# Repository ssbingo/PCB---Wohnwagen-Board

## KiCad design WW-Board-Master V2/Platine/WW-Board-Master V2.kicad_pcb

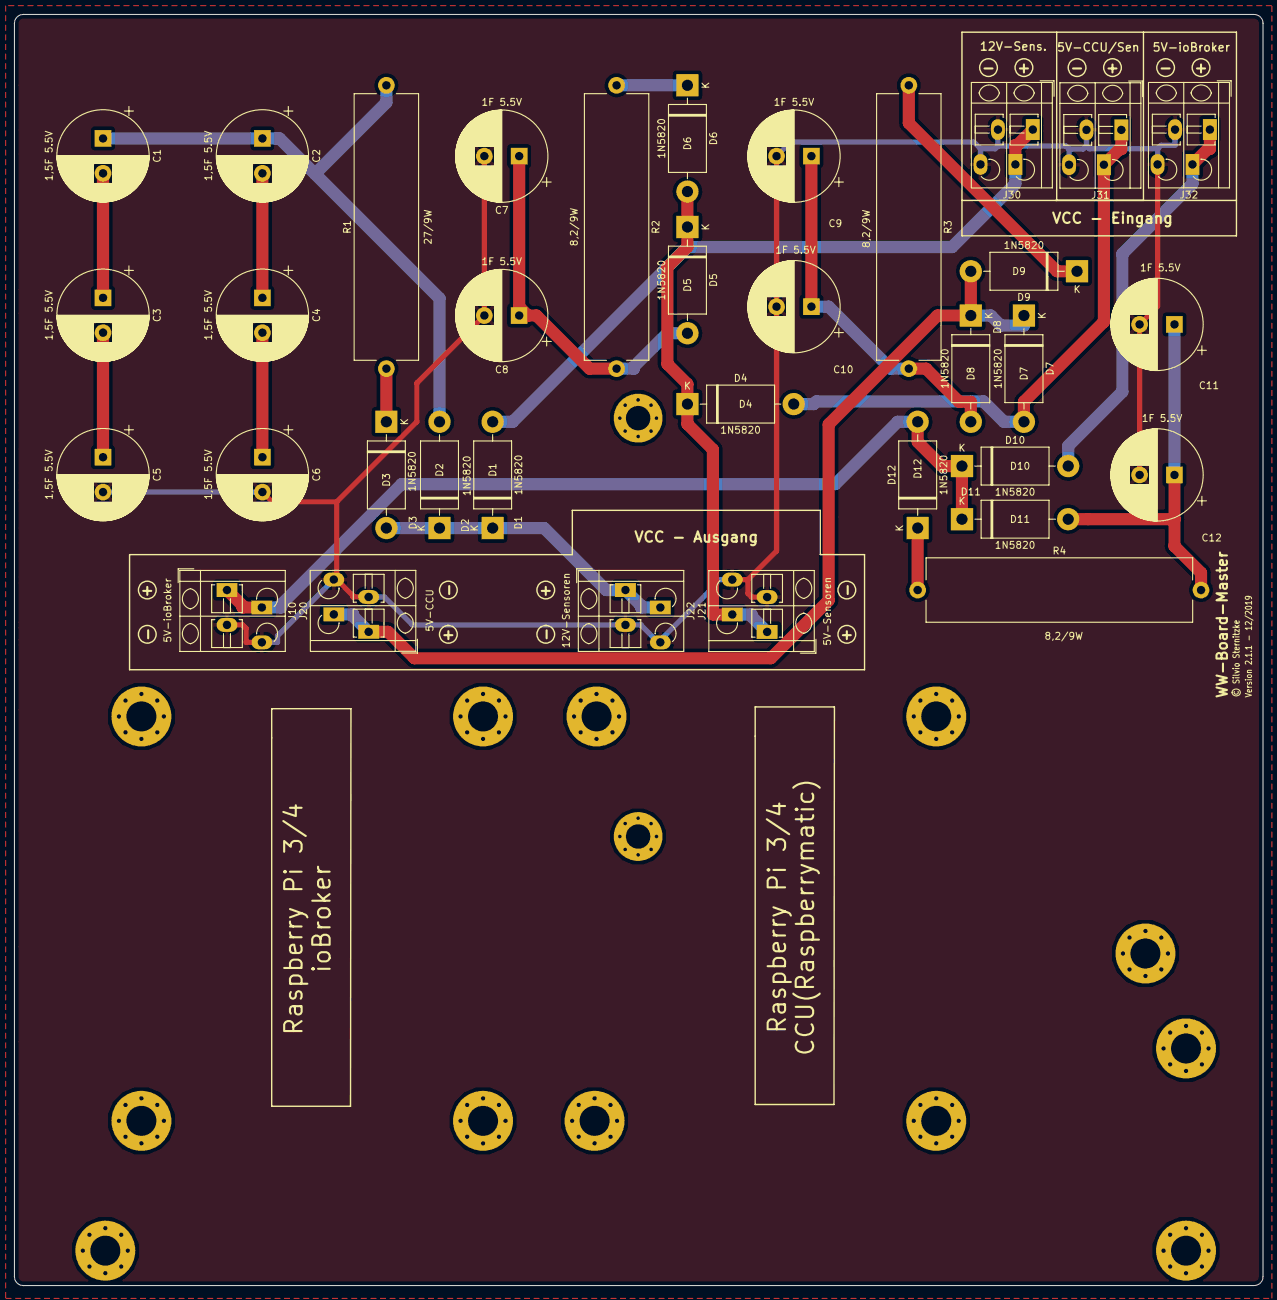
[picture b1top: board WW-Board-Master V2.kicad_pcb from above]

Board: 2 copper layers, 179.1 x 182.3 mm, 51 parts (1 on the bottom side), 20 nets.

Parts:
C1, C2, C3, C4, C5, C6: 1,5F 5.5V; CP_Radial_D21.0mm_P5.00mm
C7, C8, C9, C10, C11, C12: 1F 5.5V; CP_Radial_D20.0mm_P5.00mm
D1, D2, D3, D4, D5, D6, D7, D8, D9, D10, D11, D12: 1N5820; D_DO-201AD_P15.24mm_Horizontal
J10, J32: 5V-ioBroker; TerminalBlock_WAGO_804-102_1x02_P5.00mm_45Degree
J20: 5V-CCU; TerminalBlock_WAGO_804-102_1x02_P5.00mm_45Degree
J21: 5V-Sensoren; TerminalBlock_WAGO_804-102_1x02_P5.00mm_45Degree
J22: 12V-Sensoren; TerminalBlock_WAGO_804-102_1x02_P5.00mm_45Degree
J30: 12V-Sens.; TerminalBlock_WAGO_804-102_1x02_P5.00mm_45Degree
J31: 5V-CCU/Sen; TerminalBlock_WAGO_804-102_1x02_P5.00mm_45Degree
Logo1, Logo2: Version 2.1.1 - 12/2019; Copyrigth
R1: 27/9W; R_Axial_Power_L38.0mm_W9.0mm_P40.64mm
R2, R3, R4: 8,2/9W; R_Axial_Power_L38.0mm_W9.0mm_P40.64mm
REF05: MountingHole_4.3mm_M4_Pad_Via
REF_01, REF_02, REF_03, REF_04, REF_06, REF_07, REF_08, REF_09_1, REF_09_2, REF_09_3, REF_09_4: MountingHole_4.3mm_M4_Pad_Via
REF_S1, REF_S2: MountingHole_3.5mm_Pad_Via

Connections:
GND: C5.2, C6.2, C7.2, C8.2, C9.2, C10.2, C11.2, C12.2, J10.2, J20.2, J21.2, J22.2, J30.2, J31.2, J32.2
unnamed: C1.1, C2.1, D2.2, R1.2
unnamed: C1.2, C3.1
unnamed: C2.2, C4.1
unnamed: C3.2, C5.1
unnamed: C4.2, C6.1
unnamed: C7.1, C8.1, D5.2, R2.2
unnamed: C9.1, C10.1, D8.2, R3.2
unnamed: C11.1, C12.1, D11.2, R4.2
unnamed: D1.1, D2.1, D3.2, J22.1
unnamed: D1.2, J30.1
unnamed: D3.1, R1.1
unnamed: D4.1, D5.1, D6.2, J21.1
unnamed: D4.2, D7.2, J31.1
unnamed: D6.1, R2.1
unnamed: D7.1, D8.1, D9.2, J20.1
unnamed: D9.1, R3.1
unnamed: D10.1, D11.1, D12.2, J10.1
unnamed: D10.2, J32.1
unnamed: D12.1, R4.1

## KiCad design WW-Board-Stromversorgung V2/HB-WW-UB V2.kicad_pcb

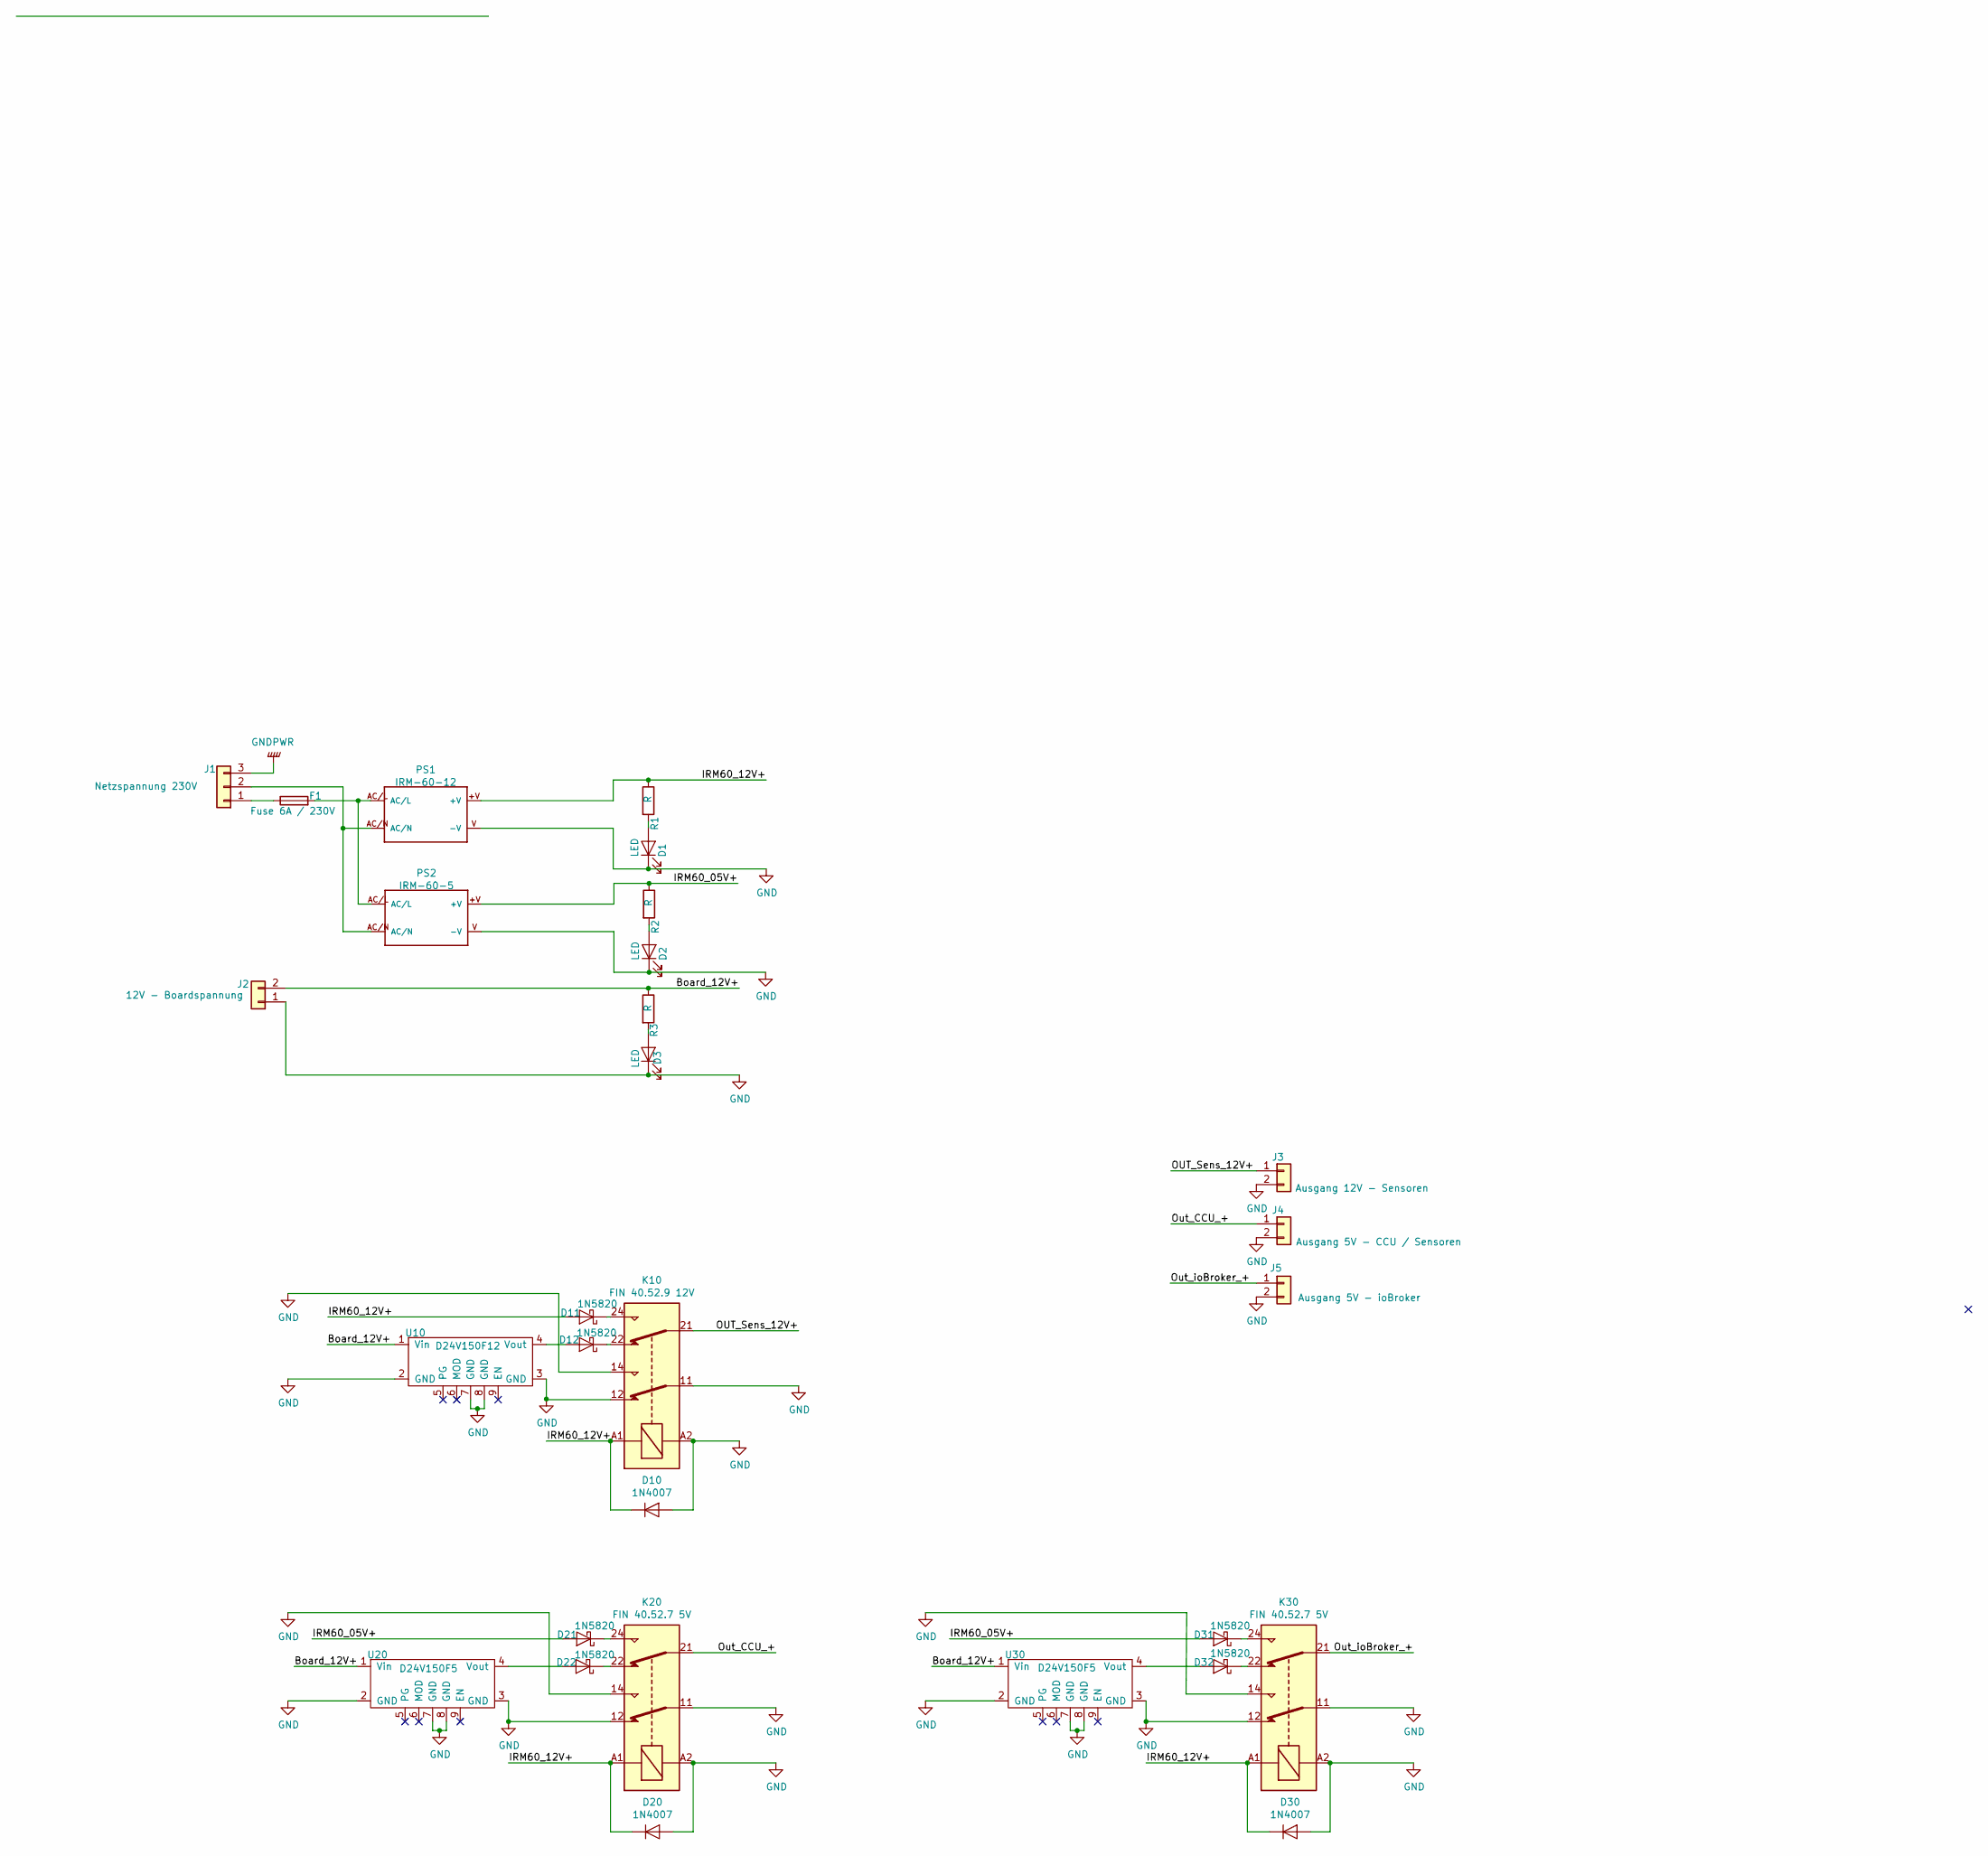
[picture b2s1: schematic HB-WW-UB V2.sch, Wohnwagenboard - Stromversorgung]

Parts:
D1, D2, D3: LED; Molex_SPOX_5267-02A_1x02_P2.50mm_Vertical
D10, D20, D30: 1N4007; D_DO-41_SOD81_P10.16mm_Horizontal
D11, D12, D21, D22, D31, D32: 1N5820; D_DO-201AD_P15.24mm_Horizontal
F1: Fuse 6A / 230V; Fuseholder_Cylinder-5x20mm_Schurter_FUP_0031.2510_Horizonta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
J1: Netzspannung 230V; Wago_734-163_1x03_P3.50mm_Horizontal
J2: 12V - Boardspannung; Wago_734-162_1x02_P3.50mm_Horizontal
J3: Ausgang 12V - Sensoren; Wago_734-162_1x02_P3.50mm_Horizontal
J4: Ausgang 5V - CCU / Sensoren; Wago_734-162_1x02_P3.50mm_Horizontal
J5: Ausgang 5V - ioBroker; Wago_734-162_1x02_P3.50mm_Horizontal
K10: FIN 40.52.9 12V; Relay_DPDT_Finder_40.52
K20, K30: FIN 40.52.7 5V; Relay_DPDT_Finder_40.52
PS1: IRM-60-12; CONV_IRM-60-12
PS2: IRM-60-5; CONV_IRM-60-12
R1, R2, R3: R; R_Axial_DIN0207_L6.3mm_D2.5mm_P2.54mm_Vertical
U10: D24V150F12; D24V150F5
U20, U30: D24V150F5

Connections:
/Board_12V+: J2.2, R3.1, U10.1 (Vin), U20.1 (Vin), U30.1 (Vin)
/IRM60_05V+: D21.2 (A), D31.2 (A), PS2.+V, R2.1
/IRM60_12V+: D10.1 (K), D11.2 (A), D20.1 (K), D30.1 (K), K10.A1, K20.A1, K30.A1, PS1.+V, R1.1
/OUT_Sens_12V+: J3.1, K10.21
/Out_CCU_+: J4.1, K20.21
/Out_ioBroker_+: J5.1, K30.21
GND: D1.1 (K), D2.1 (K), D3.1 (K), D10.2 (A), D20.2 (A), D30.2 (A), J2.1, J3.2, J4.2, J5.2, K10.11, K10.12, K10.14, K10.A2, K20.11, K20.12, K20.14, K20.A2, K30.11, K30.12, K30.14, K30.A2, PS1.V (-V), PS2.V (-V), U10.2 (GND), U10.3 (GND), U10.7 (GND), U10.8 (GND), U20.2 (GND), U20.3 (GND), U20.7 (GND), U20.8 (GND), U30.2 (GND), U30.3 (GND), U30.7 (GND), U30.8 (GND)
GNDPWR: J1.3
unnamed: D1.2 (A), R1.2
unnamed: D2.2 (A), R2.2
unnamed: D3.2 (A), R3.2
unnamed: D11.1 (K), K10.24
unnamed: D12.1 (K), K10.22
unnamed: D12.2 (A), U10.4 (Vout)
unnamed: D21.1 (K), K20.24
unnamed: D22.1 (K), K20.22
unnamed: D22.2 (A), U20.4 (Vout)
unnamed: D31.1 (K), K30.24
unnamed: D32.1 (K), K30.22
unnamed: D32.2 (A), U30.4 (Vout)
unnamed: F1.1, J1.1
unnamed: F1.2, PS1.AC/L, PS2.AC/L
unnamed: J1.2, PS1.AC/N, PS2.AC/N

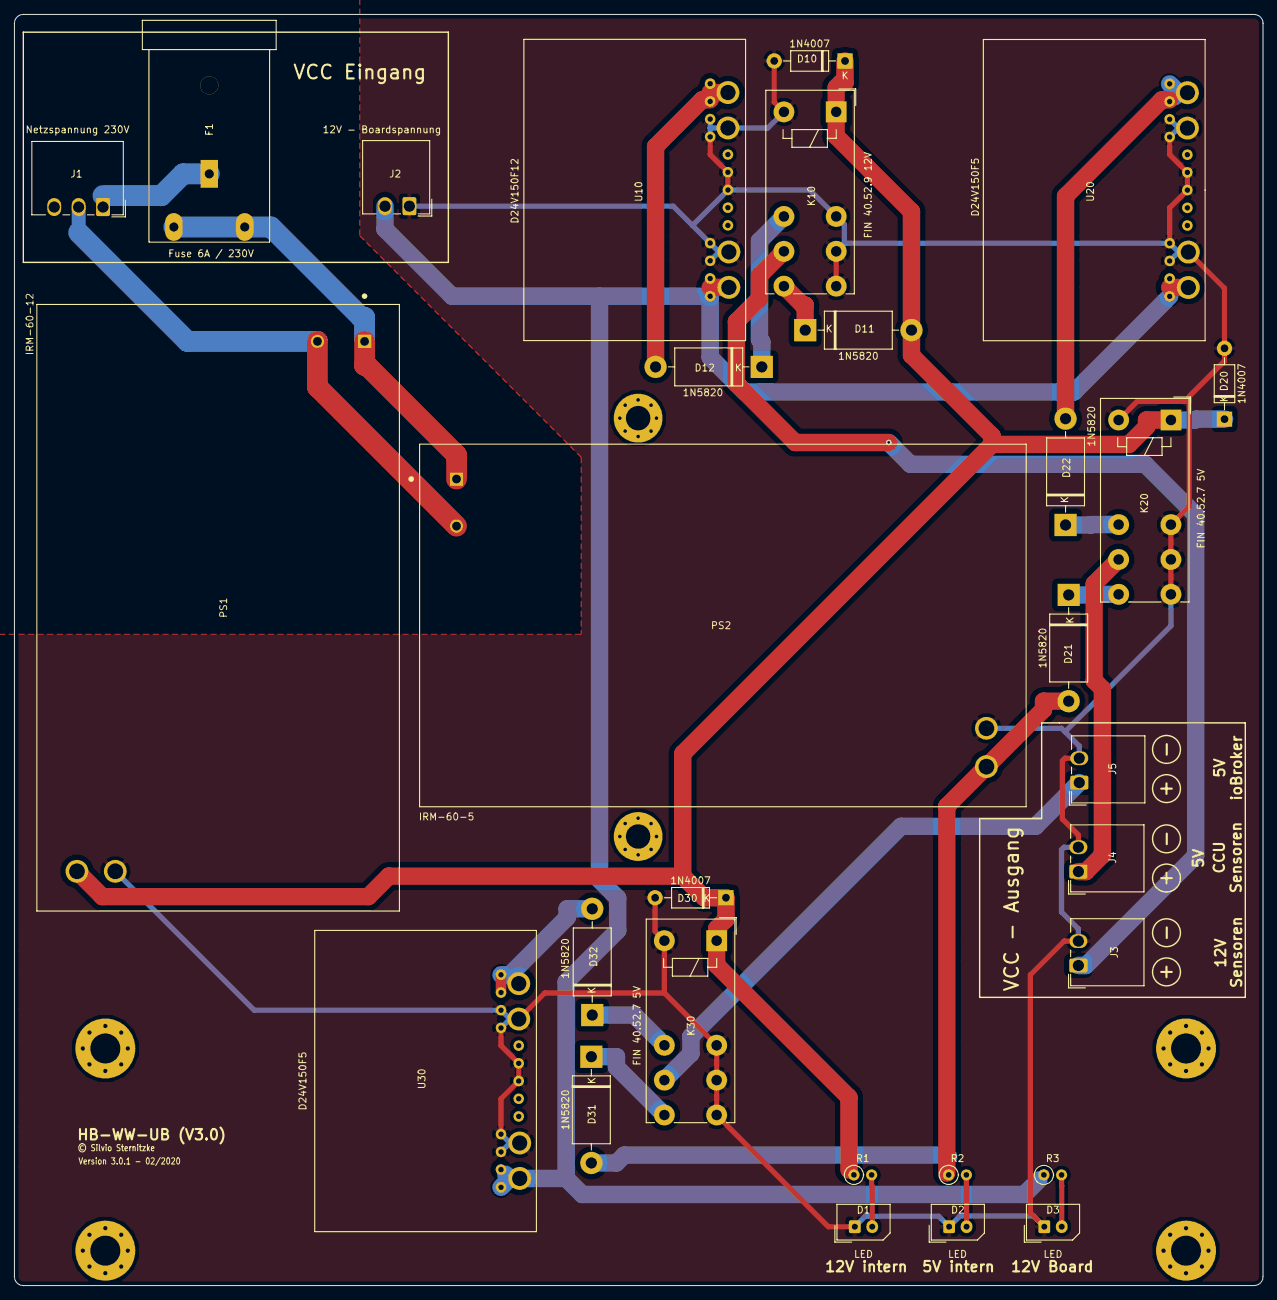
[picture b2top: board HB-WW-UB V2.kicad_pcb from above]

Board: 2 copper layers, 179.1 x 182.3 mm, 37 parts (1 on the bottom side), 22 nets.

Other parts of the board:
Copy01, Copy02: Version 3.0.1 - 02/2020; Copyrigth
REF_09, REF_10, REF_11, REF_12: MountingHole_4.3mm_M4_Pad_Via
REF_S1, REF_S2: MountingHole_3.5mm_Pad_Via

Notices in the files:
WW-Board-Stromversorgung V2/HB-WW-UB V2.sch:
©Slvio Sternitzke
parts and their libraries:
© Silvio Sternitzke
